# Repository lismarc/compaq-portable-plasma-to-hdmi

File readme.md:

Hi, this is Marcin @hawix (father) and Kuba @qbus (son).

We are members of the [Polish Society for the Protection of Technical Heritage - Polskie Towarzystwo Ochrony Dziedzictwa Technicznego (PTODT)](https://ptodt.org.pl/). From time to time, we manage to bring old computers back to life. It's our shared passion. We spend time together and learn about electronics, computer science, computer system architecture, and their history. 

We summarize the results of our work at events organized by PTODT, called KWAS.

---

In 2025, Kuba received an iconic **Compaq Portable III** computer from Szymon @sajmosia. The computer was complete, but its plasma screen was broken.

We decided to resurrect this computer. 
The project presented here is the result of our work. The broken plasma screen is beyond repair, but we came up with the idea of ​​replacing the screen with a modern LCD screen with an HDMI connector. 

To achieve this, we analyzed the signals reaching the display. We designed a simple FPGA-based circuit that decodes signals and converts them into an HDMI stream.

---

On Saturday, June 26, 2025, the 40th KWAS meeting took place in Katowice, where we presented our joint adventure of restoring a donated computer. 
**[You can watch it here, paste a link]** *(Note: insert video link here)*. There, we discuss how it works.

We know that many Compaq Portable III computers experience screen problems for various reasons. We hope this project will help bring your computer back to life.

### We are sharing all project files:

* 📁 **`fpga-tang-nano`**  
  Verilog source code for the Tang Nano 9K platform. This is a very inexpensive circuit with a low entry threshold for amateurs. The FPGA configuration is written in the [Gowin IDE](https://www.gowinsemi.com/en/support/home). You can build a bitstream for this circuit yourself and transfer it to the flash memory via USB-C.

* 📁 **`Schematics-kicad`**  
  Schematic of a board with a voltage converter from 5V logic signals from the Compaq to the 3.3V logic required by the Tang Nano. The board is designed as a shield that attaches to the back of the Tang Nano 9K to minimize space and fit inside the display case. It also includes a USB connector for powering the display. The catalog also includes ready-made Gerber files, which you can submit to PCBWay or similar companies.

* 📁 **`adapter-fussion360`**  
  3D printable LCD screen adapter design. We used dispaly ELCROW 10,1" 1280x800  that can perfectly can be fitted into CPIII disaply panel.

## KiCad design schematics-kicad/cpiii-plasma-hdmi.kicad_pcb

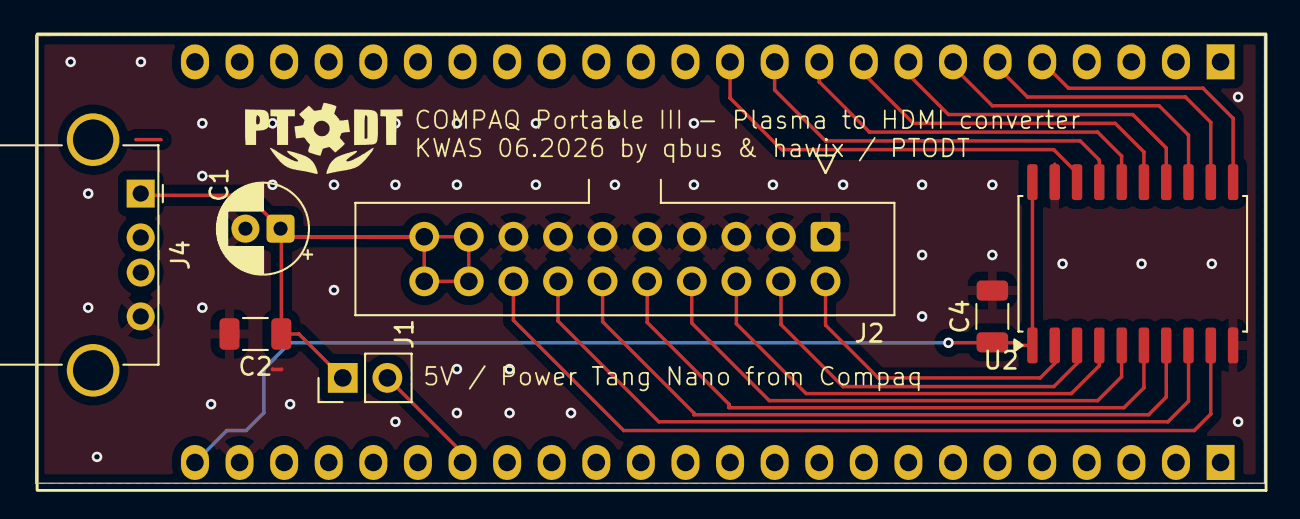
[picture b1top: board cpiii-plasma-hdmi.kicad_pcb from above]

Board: 2 copper layers, 70.0 x 25.5 mm, 9 parts (0 on the bottom side), 20 nets.

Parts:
C1: 10uF; CP_Radial_D5.0mm_P2.00mm
C2, C4: 100nF; C_1206_3216Metric
J1: Power Tang Nano from Compaq; PinHeader_1x02_P2.54mm_Vertical
J2: PLASMA_CONNECTOR; IDC-Header_2x10-1MP_P2.54mm_Latch6.5mm_Vertical
J4: USB_A; USB_A_Stewart_SS-52100-001_Horizontal
U1: Tang_Nano_9K; DIP-48_TangNano9K
U2: SN74LVC245A; SOIC-20W_7.5x12.8mm_P1.27mm
a: LOGO; ptodt

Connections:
3V3: C4.1, U1.25 (3V3), U2.1 (DIR), U2.20 (Vcc)
/PLS_DATA0: J2.16, U2.9 (A8)
/PLS_DATA1: J2.14, U2.8 (A7)
/PLS_DATA2: J2.12, U2.7 (A6)
/PLS_DATA3: J2.10, U2.6 (A5)
/PLS_ENA: J2.2, U2.2 (A1)
/PLS_HS: J2.6, U2.4 (A3)
/PLS_PCLK: J2.8, U2.5 (A4)
/PLS_VS: J2.4, U2.3 (A2)
/TG_5V: J1.2, U1.31 (5V)
/TG_DATA0: U1.5 (25_IOB8A), U2.11 (B8)
/TG_DATA1: U1.6 (26_IOB8B), U2.12 (B7)
/TG_DATA2: U1.7 (27_IOB11A), U2.13 (B6)
/TG_DATA3: U1.8 (28_IOB11B), U2.14 (B5)
/TG_ENA: U1.12 (34_IOB23B), U2.18 (B1)
/TG_HS: U1.10 (30_IOB13B), U2.16 (B3)
/TG_PCLK: U1.9 (29_IOB13A), U2.15 (B4)
/TG_VS: U1.11 (33_IOB23A), U2.17 (B2)
GND: C1.2, C2.2, C4.2, J2.1, J2.3, J2.5, J2.7, J2.9, J2.11, J2.13, J2.15, J4.4 (GND), U1.26 (GND), U2.10 (GND), U2.19 (~OE)
PLS_VDC: C1.1, C2.1, J1.1, J2.17, J2.18, J2.19, J2.20, J4.1 (VBUS)
